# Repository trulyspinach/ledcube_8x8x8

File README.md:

# ledcube_8x8x8

Hobby Compact LED Cube.

Please beware that I'm not a professional electrical enginner, this project is just me having fun. I provide absolutely no warranty for this :)

## The hardware build

My goal is to build a compact LED cube. A lot of cube built i found on Internet is huge(kind of, at least you can't carry them with you), even when the resolution is 8x8x8. So I chose to use small LEDs, and a printed circuit board to hold them together while providing control circuits.

The microcontroller is Atmega32A, the reason of choosing AVR is just because they are simple and really cheap to get, and the 32A model have a fairly enough amount of pins available. Then eight 574s are used for multiplexing IOs. No big deals, pretty simple.

To build this, all you need is around 6 hundreds of LEDs. Only 512 are needed, but when you purchasing cheap LEDs, it is likely that some of them will malfunctions. And some resisitor, caps for the motherboard.

I got all components on local stores and AliExpress, the complete built cost me less than $10(surprisingly cheap huh?).

## Software.

Well, since it is an Atmega32A, you can totaly program it using Arduino IDE(You don't need to).
I haven't had enough time to write some beautiful program yet, but the demo code included is just enough to test and proof your circuit is working.

Yes I will put more code here later..

## Did I made a video ?

Yes, it is here: https://www.bilibili.com/video/av40196289/

The voiceover is me speaking Chinese, but it should be fine.

## Where to get PCBs?

I did included all board layout file in the repo, you can export them with Eagle to some manufactor to made them.
As you know, those manufactors don't really like to just make one board, so I have some spare boards in my hand. I can ship one to you if you live in China, and if by the time you contact me I still have them..

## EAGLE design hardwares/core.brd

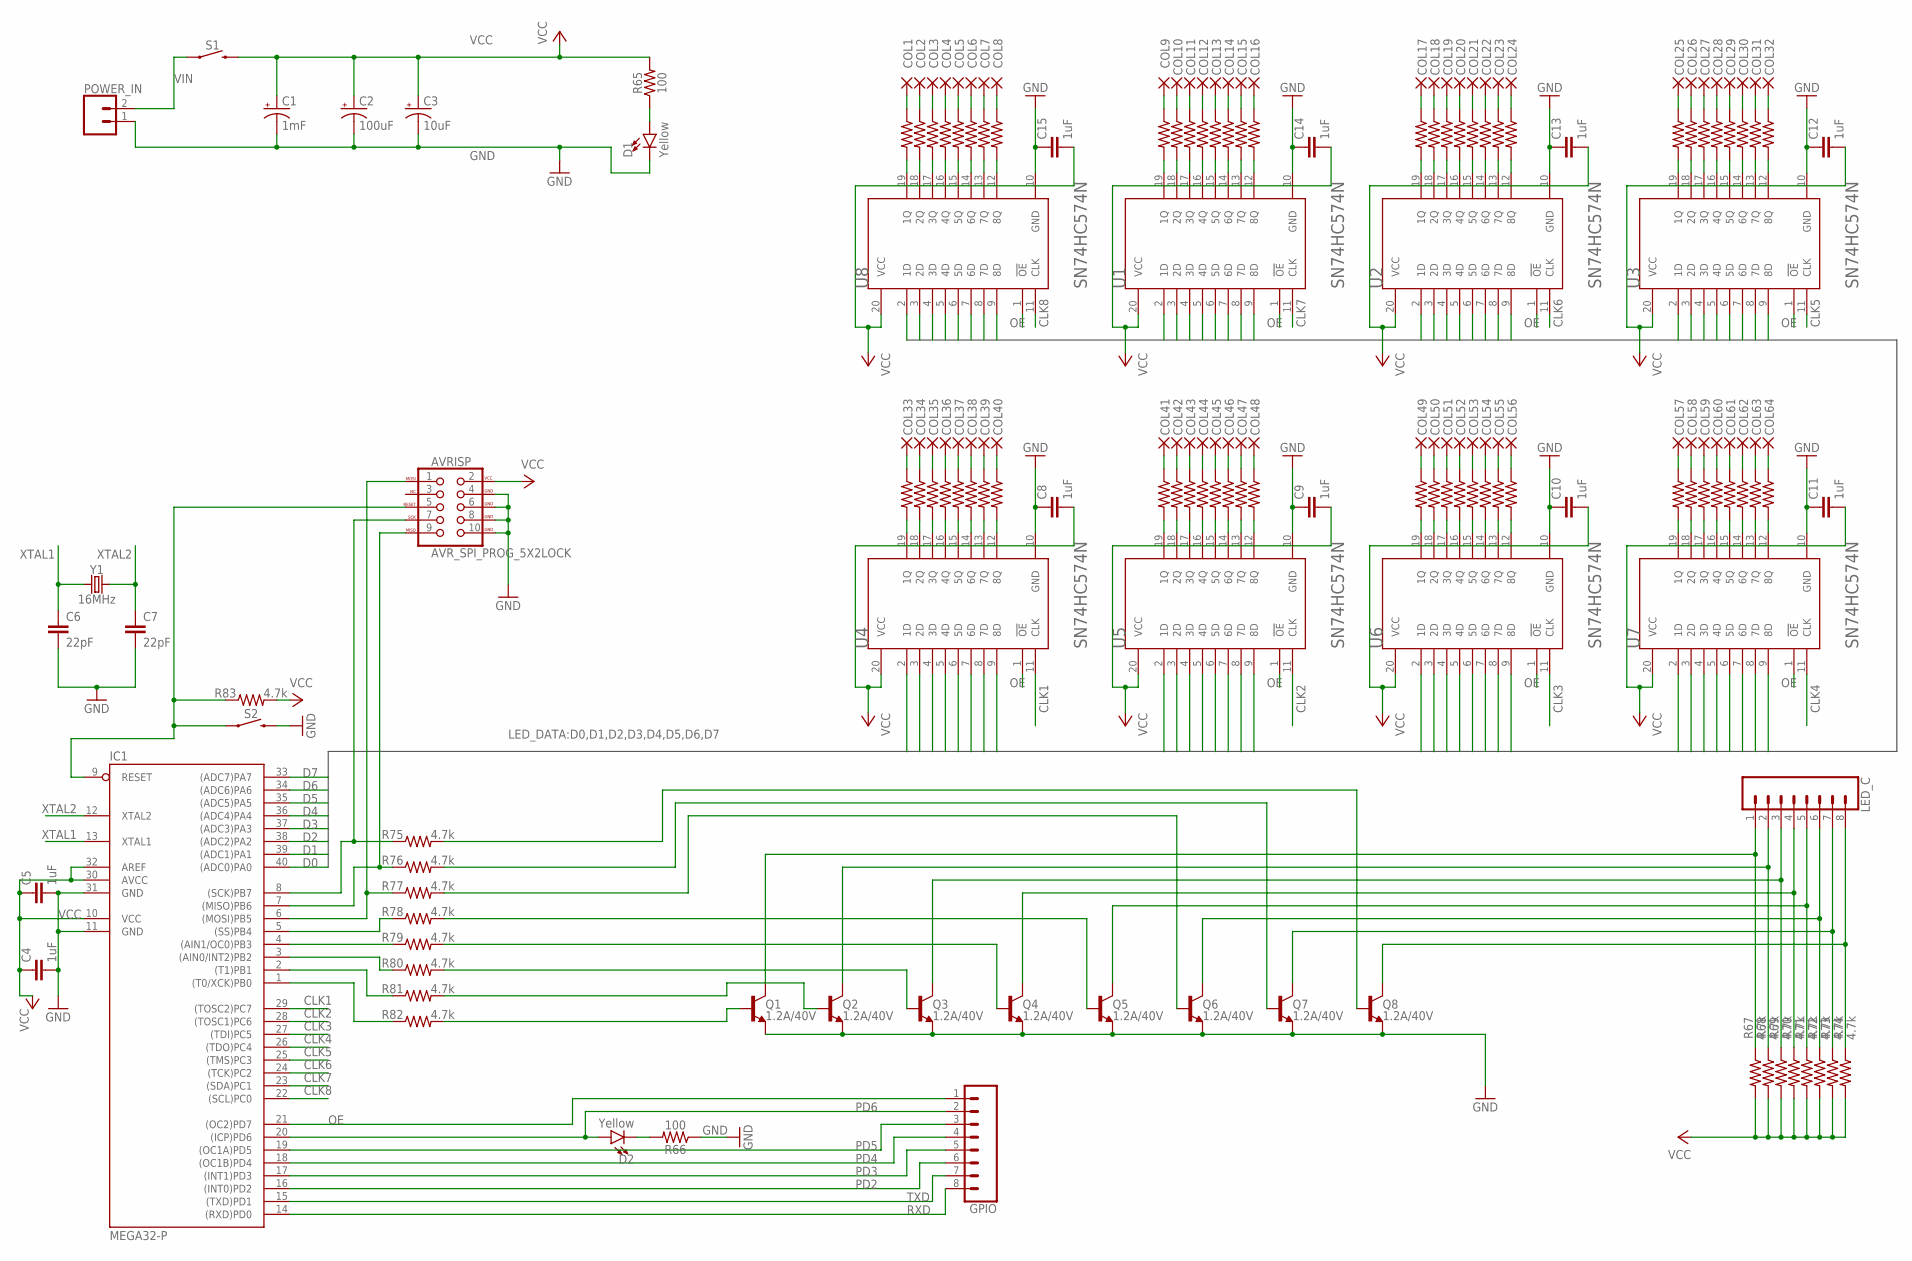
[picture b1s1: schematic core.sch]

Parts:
AVRISP: AVR_SPI_PROG_5X2LOCK; 2X5-SHROUDED_LOCK
C1: 1mF; CPOL-RADIAL-5MM-10MM
C2: 100uF; CPOL-RADIAL-2.5MM-6.5MM
C3: 10uF; CPOL-RADIAL-2.5MM-5MM
C4, C5, C8, C9, C10, C11, C12, C13, C14, C15: 1uF; C2.5-3
C6, C7: 22pF; CAP-PTH-2.54
COL1, COL2, COL3, COL4, COL5, COL6, COL7, COL8, COL9, COL10, COL11, COL12, COL13, COL14, COL15, COL16, COL17, COL18, COL19, COL20, COL21, COL22, COL23, COL24, COL25, COL26, COL27, COL28, COL29, COL30, COL31, COL32, COL33, COL34, COL35, COL36, COL37, COL38, COL39, COL40, COL41, COL42, COL43, COL44, COL45, COL46, COL47, COL48, COL49, COL50, COL51, COL52, COL53, COL54, COL55, COL56, COL57, COL58, COL59, COL60, COL61, COL62, COL63, COL64: 1,6/0,9
D1, D2: Yellow; LED-1206
GPIO: CONN_08"; 1X08
IC1: MEGA32-P; DIL40
LED_C: CONN_08"; 1X08
POWER_IN: CONN_02POLAR; MOLEX-1X2
Q1, Q2, Q3, Q4, Q5, Q6, Q7, Q8: 1.2A/40V; SOT23-3
R1, R2, R3, R4, R5, R6, R7, R8, R9, R10, R11, R12, R13, R14, R15, R16, R17, R18, R19, R20, R21, R22, R23, R24, R25, R26, R27, R28, R29, R30, R31, R32, R33, R34, R35, R36, R37, R38, R39, R40, R41, R42, R43, R44, R45, R46, R47, R48, R49, R50, R51, R52, R53, R54, R55, R56, R57, R58, R59, R60, R61, R62, R63, R64, R65, R66: 100; AXIAL-0.3
R67, R68, R69, R70, R71, R72, R73, R74, R75, R76, R77, R78, R79, R80, R81, R82, R83: 4.7k; AXIAL-0.3
S1: MOMENTARY-SWITCH-SPST-PTH-RIGHT-ANGLE-KIT; TACTILE_SWITCH_PTH_RIGHT_ANGLE_KIT
S2: MOMENTARY-SWITCH-SPST-PTH-6.0MM; TACTILE_SWITCH_PTH_6.0MM
U1, U2, U3, U4, U5, U6, U7, U8: TEXAS_INSTRUMENTS_SN74HC574NTEXAS_INSTRUMENTS_SN7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; TEXAS_INSTRUMENTS_SN74HC574N_0
Y1: 16MHz; HC49US

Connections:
CLK1: IC1.29 ((TOSC2)PC7), U4.11 (CLK)
CLK2: IC1.28 ((TOSC1)PC6), U5.11 (CLK)
CLK3: IC1.27 ((TDI)PC5), U6.11 (CLK)
CLK4: IC1.26 ((TDO)PC4), U7.11 (CLK)
CLK5: IC1.25 ((TMS)PC3), U3.11 (CLK)
CLK6: IC1.24 ((TCK)PC2), U2.11 (CLK)
CLK7: IC1.23 ((SDA)PC1), U1.11 (CLK)
CLK8: IC1.22 ((SCL)PC0), U8.11 (CLK)
D0: IC1.40 ((ADC0)PA0), U1.2 (1D), U2.2 (1D), U3.2 (1D), U4.2 (1D), U5.2 (1D), U6.2 (1D), U7.2 (1D), U8.2 (1D)
D1: IC1.39 ((ADC1)PA1), U1.3 (2D), U2.3 (2D), U3.3 (2D), U4.3 (2D), U5.3 (2D), U6.3 (2D), U7.3 (2D), U8.3 (2D)
D2: IC1.38 ((ADC2)PA2), U1.4 (3D), U2.4 (3D), U3.4 (3D), U4.4 (3D), U5.4 (3D), U6.4 (3D), U7.4 (3D), U8.4 (3D)
D3: IC1.37 ((ADC3)PA3), U1.5 (4D), U2.5 (4D), U3.5 (4D), U4.5 (4D), U5.5 (4D), U6.5 (4D), U7.5 (4D), U8.5 (4D)
D4: IC1.36 ((ADC4)PA4), U1.6 (5D), U2.6 (5D), U3.6 (5D), U4.6 (5D), U5.6 (5D), U6.6 (5D), U7.6 (5D), U8.6 (5D)
D5: IC1.35 ((ADC5)PA5), U1.7 (6D), U2.7 (6D), U3.7 (6D), U4.7 (6D), U5.7 (6D), U6.7 (6D), U7.7 (6D), U8.7 (6D)
D6: IC1.34 ((ADC6)PA6), U1.8 (7D), U2.8 (7D), U3.8 (7D), U4.8 (7D), U5.8 (7D), U6.8 (7D), U7.8 (7D), U8.8 (7D)
D7: IC1.33 ((ADC7)PA7), U1.9 (8D), U2.9 (8D), U3.9 (8D), U4.9 (8D), U5.9 (8D), U6.9 (8D), U7.9 (8D), U8.9 (8D)
GND: AVRISP.4 (GND), AVRISP.6 (GND), AVRISP.8 (GND), AVRISP.10 (GND), C1.-, C2.2 (-), C3.2 (-), C4.2, C5.2, C6.2, C7.2, C8.1, C9.1, C10.1, C11.1, C12.1, C13.1, C14.1, C15.1, D1.C, IC1.11 (GND), IC1.31 (GND), POWER_IN.1, Q1.2 (E), Q2.2 (E), Q3.2 (E), Q4.2 (E), Q5.2 (E), Q6.2 (E), Q7.2 (E), Q8.2 (E), R66.P$1 (1), S2.3 (2), U1.10 (GND), U2.10 (GND), U3.10 (GND), U4.10 (GND), U5.10 (GND), U6.10 (GND), U7.10 (GND), U8.10 (GND)
unnamed: COL1.1, R1.P$1 (1)
unnamed: R1.P$2 (2), U8.19 (1Q)
unnamed: COL2.1, R2.P$1 (1)
unnamed: R2.P$2 (2), U8.18 (2Q)
unnamed: COL3.1, R3.P$1 (1)
unnamed: R3.P$2 (2), U8.17 (3Q)
unnamed: COL4.1, R4.P$1 (1)
unnamed: R4.P$2 (2), U8.16 (4Q)
unnamed: COL5.1, R5.P$1 (1)
unnamed: R5.P$2 (2), U8.15 (5Q)
unnamed: COL6.1, R6.P$1 (1)
unnamed: R6.P$2 (2), U8.14 (6Q)
unnamed: COL7.1, R7.P$1 (1)
unnamed: R7.P$2 (2), U8.13 (7Q)
unnamed: COL8.1, R8.P$1 (1)
unnamed: R8.P$2 (2), U8.12 (8Q)
unnamed: COL9.1, R9.P$1 (1)
unnamed: R9.P$2 (2), U1.19 (1Q)
unnamed: COL10.1, R10.P$1 (1)
unnamed: R10.P$2 (2), U1.18 (2Q)
unnamed: COL11.1, R11.P$1 (1)
unnamed: R11.P$2 (2), U1.17 (3Q)
unnamed: COL12.1, R12.P$1 (1)
unnamed: R12.P$2 (2), U1.16 (4Q)
unnamed: COL13.1, R13.P$1 (1)
unnamed: R13.P$2 (2), U1.15 (5Q)
unnamed: COL14.1, R14.P$1 (1)
unnamed: R14.P$2 (2), U1.14 (6Q)
unnamed: COL15.1, R15.P$1 (1)
unnamed: R15.P$2 (2), U1.13 (7Q)
unnamed: COL16.1, R16.P$1 (1)
unnamed: R16.P$2 (2), U1.12 (8Q)
unnamed: COL17.1, R17.P$1 (1)
unnamed: R17.P$2 (2), U2.19 (1Q)
unnamed: COL18.1, R18.P$1 (1)
unnamed: R18.P$2 (2), U2.18 (2Q)
unnamed: COL19.1, R19.P$1 (1)
unnamed: R19.P$2 (2), U2.17 (3Q)
unnamed: COL20.1, R20.P$1 (1)
unnamed: R20.P$2 (2), U2.16 (4Q)
unnamed: COL21.1, R21.P$1 (1)
unnamed: R21.P$2 (2), U2.15 (5Q)
unnamed: COL22.1, R22.P$1 (1)
unnamed: R22.P$2 (2), U2.14 (6Q)
unnamed: COL23.1, R23.P$1 (1)
unnamed: R23.P$2 (2), U2.13 (7Q)
unnamed: COL24.1, R24.P$1 (1)
unnamed: R24.P$2 (2), U2.12 (8Q)
unnamed: COL25.1, R25.P$1 (1)
unnamed: R25.P$2 (2), U3.19 (1Q)
unnamed: COL26.1, R26.P$1 (1)
unnamed: R26.P$2 (2), U3.18 (2Q)
unnamed: COL27.1, R27.P$1 (1)
unnamed: R27.P$2 (2), U3.17 (3Q)
unnamed: COL28.1, R28.P$1 (1)
unnamed: R28.P$2 (2), U3.16 (4Q)
unnamed: COL29.1, R29.P$1 (1)
unnamed: R29.P$2 (2), U3.15 (5Q)
unnamed: COL30.1, R30.P$1 (1)
unnamed: R30.P$2 (2), U3.14 (6Q)
unnamed: COL31.1, R31.P$1 (1)
unnamed: R31.P$2 (2), U3.13 (7Q)
unnamed: COL32.1, R32.P$1 (1)
unnamed: R32.P$2 (2), U3.12 (8Q)
unnamed: COL33.1, R33.P$1 (1)
unnamed: R33.P$2 (2), U4.19 (1Q)
unnamed: COL34.1, R34.P$1 (1)
unnamed: R34.P$2 (2), U4.18 (2Q)
unnamed: COL35.1, R35.P$1 (1)
unnamed: R35.P$2 (2), U4.17 (3Q)
unnamed: COL36.1, R36.P$1 (1)
unnamed: R36.P$2 (2), U4.16 (4Q)
unnamed: COL37.1, R37.P$1 (1)
unnamed: R37.P$2 (2), U4.15 (5Q)
unnamed: COL38.1, R38.P$1 (1)
unnamed: R38.P$2 (2), U4.14 (6Q)
unnamed: COL39.1, R39.P$1 (1)
unnamed: R39.P$2 (2), U4.13 (7Q)
unnamed: COL40.1, R40.P$1 (1)
unnamed: R40.P$2 (2), U4.12 (8Q)
unnamed: COL41.1, R41.P$1 (1)
unnamed: R41.P$2 (2), U5.19 (1Q)
unnamed: COL42.1, R42.P$1 (1)
unnamed: R42.P$2 (2), U5.18 (2Q)
unnamed: COL43.1, R43.P$1 (1)
unnamed: R43.P$2 (2), U5.17 (3Q)
unnamed: COL44.1, R44.P$1 (1)
unnamed: R44.P$2 (2), U5.16 (4Q)
unnamed: COL45.1, R45.P$1 (1)
unnamed: R45.P$2 (2), U5.15 (5Q)
unnamed: COL46.1, R46.P$1 (1)
unnamed: R46.P$2 (2), U5.14 (6Q)
unnamed: COL47.1, R47.P$1 (1)
unnamed: R47.P$2 (2), U5.13 (7Q)
unnamed: COL48.1, R48.P$1 (1)
unnamed: R48.P$2 (2), U5.12 (8Q)
unnamed: COL49.1, R49.P$1 (1)
unnamed: R49.P$2 (2), U6.19 (1Q)
unnamed: COL50.1, R50.P$1 (1)
unnamed: R50.P$2 (2), U6.18 (2Q)
unnamed: COL51.1, R51.P$1 (1)
unnamed: R51.P$2 (2), U6.17 (3Q)
unnamed: COL52.1, R52.P$1 (1)
unnamed: R52.P$2 (2), U6.16 (4Q)
unnamed: COL53.1, R53.P$1 (1)
unnamed: R53.P$2 (2), U6.15 (5Q)
unnamed: COL54.1, R54.P$1 (1)
unnamed: R54.P$2 (2), U6.14 (6Q)
unnamed: COL55.1, R55.P$1 (1)
unnamed: R55.P$2 (2), U6.13 (7Q)
unnamed: COL56.1, R56.P$1 (1)
unnamed: R56.P$2 (2), U6.12 (8Q)
unnamed: COL57.1, R57.P$1 (1)
unnamed: R57.P$2 (2), U7.19 (1Q)
unnamed: COL58.1, R58.P$1 (1)
unnamed: R58.P$2 (2), U7.18 (2Q)
unnamed: COL59.1, R59.P$1 (1)
unnamed: R59.P$2 (2), U7.17 (3Q)
unnamed: COL60.1, R60.P$1 (1)
unnamed: R60.P$2 (2), U7.16 (4Q)
unnamed: COL61.1, R61.P$1 (1)
unnamed: R61.P$2 (2), U7.15 (5Q)
unnamed: COL62.1, R62.P$1 (1)
unnamed: R62.P$2 (2), U7.14 (6Q)
unnamed: COL63.1, R63.P$1 (1)
unnamed: R63.P$2 (2), U7.13 (7Q)
unnamed: COL64.1, R64.P$1 (1)
unnamed: R64.P$2 (2), U7.12 (8Q)
unnamed: D1.A, R65.P$1 (1)
unnamed: D2.C, R66.P$2 (2)
unnamed: LED_C.1, Q1.3 (C), R67.P$1 (1)
unnamed: LED_C.2, Q2.3 (C), R68.P$1 (1)
unnamed: LED_C.3, Q3.3 (C), R69.P$1 (1)
unnamed: LED_C.4, Q4.3 (C), R70.P$1 (1)
unnamed: LED_C.5, Q5.3 (C), R71.P$1 (1)
unnamed: LED_C.6, Q6.3 (C), R72.P$1 (1)
unnamed: LED_C.7, Q7.3 (C), R73.P$1 (1)
unnamed: LED_C.8, Q8.3 (C), R74.P$1 (1)
unnamed: IC1.1 ((T0/XCK)PB0), R82.P$1 (1)
unnamed: IC1.2 ((T1)PB1), R81.P$1 (1)
unnamed: IC1.3 ((AIN0/INT2)PB2), R80.P$1 (1)
unnamed: IC1.4 ((AIN1/OC0)PB3), R79.P$1 (1)
unnamed: IC1.5 ((SS)PB4), R78.P$1 (1)
unnamed: AVRISP.1 (MOSI), IC1.6 ((MOSI)PB5), R77.P$1 (1)
unnamed: AVRISP.9 (MISO), IC1.7 ((MISO)PB6), R76.P$1 (1)
unnamed: AVRISP.7 (SCK), IC1.8 ((SCK)PB7), R75.P$1 (1)
unnamed: Q1.1 (B), R82.P$2 (2)
unnamed: Q2.1 (B), R81.P$2 (2)
unnamed: Q6.1 (B), R77.P$2 (2)
unnamed: Q3.1 (B), R80.P$2 (2)
unnamed: Q4.1 (B), R79.P$2 (2)
unnamed: Q5.1 (B), R78.P$2 (2)
unnamed: Q7.1 (B), R76.P$2 (2)
unnamed: Q8.1 (B), R75.P$2 (2)
unnamed: AVRISP.5 (RESET), IC1.9 (RESET), R83.P$1 (1), S2.1
OE: GPIO.1, IC1.21 ((OC2)PD7), U1.1 (!OE!), U2.1 (!OE!), U3.1 (!OE!), U4.1 (!OE!), U5.1 (!OE!), U6.1 (!OE!), U7.1 (!OE!), U8.1 (!OE!)
PD2: GPIO.6, IC1.16 ((INT0)PD2)
PD3: GPIO.5, IC1.17 ((INT1)PD3)
PD4: GPIO.4, IC1.18 ((OC1B)PD4)
PD5: GPIO.3, IC1.19 ((OC1A)PD5)
PD6: D2.A, GPIO.2, IC1.20 ((ICP)PD6)
RXD: GPIO.8, IC1.14 ((RXD)PD0)
TXD: GPIO.7, IC1.15 ((TXD)PD1)
VCC: AVRISP.2 (VCC), C1.+, C2.1 (+), C3.1 (+), C4.1, C5.1, C8.2, C9.2, C10.2, C11.2, C12.2, C13.2, C14.2, C15.2, IC1.10 (VCC), IC1.30 (AVCC), IC1.32 (AREF), R65.P$2 (2), R67.P$2 (2), R68.P$2 (2), R69.P$2 (2), R70.P$2 (2), R71.P$2 (2), R72.P$2 (2), R73.P$2 (2), R74.P$2 (2), R83.P$2 (2), S1.2, U1.20 (VCC), U2.20 (VCC), U3.20 (VCC), U4.20 (VCC), U5.20 (VCC), U6.20 (VCC), U7.20 (VCC), U8.20 (VCC)
VIN: POWER_IN.2, S1.1
XTAL1: C6.1, IC1.13 (XTAL1), Y1.1
XTAL2: C7.1, IC1.12 (XTAL2), Y1.2

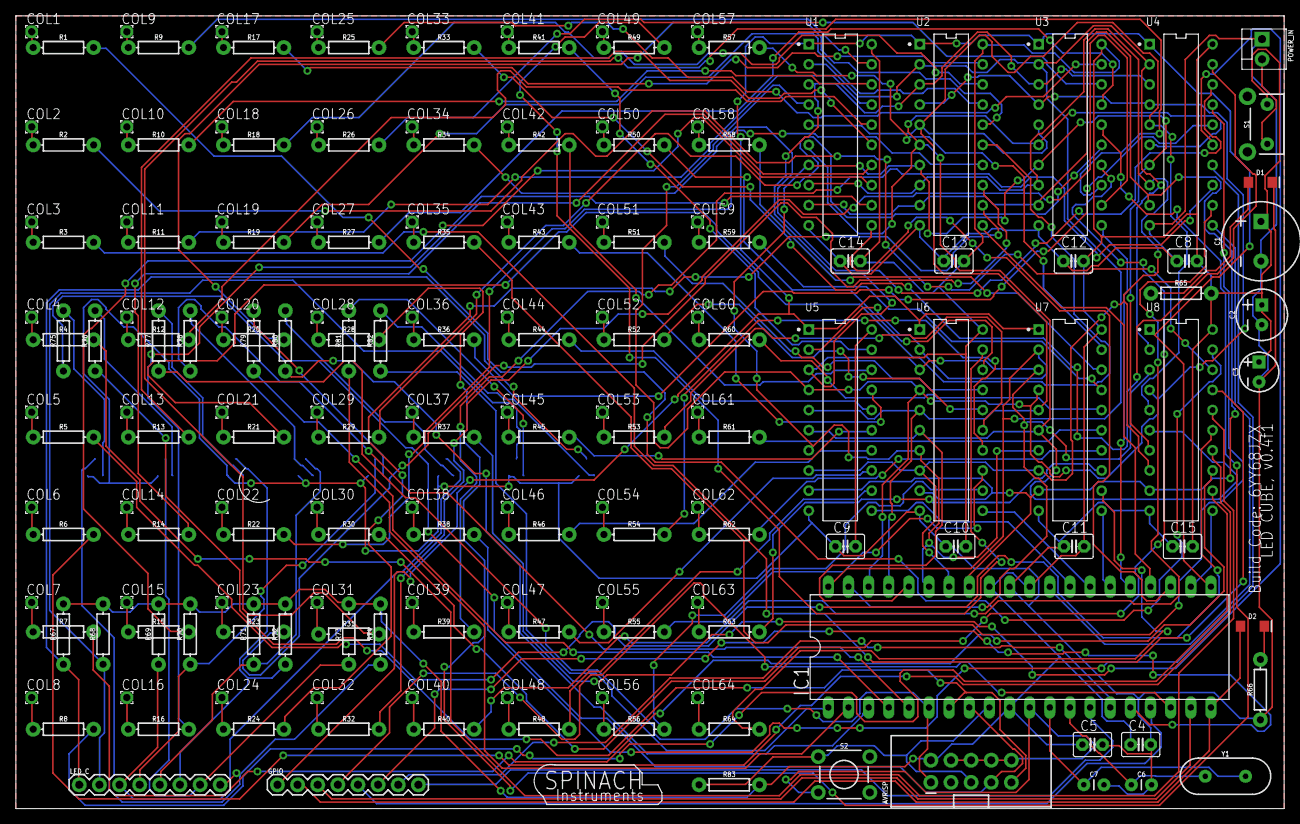
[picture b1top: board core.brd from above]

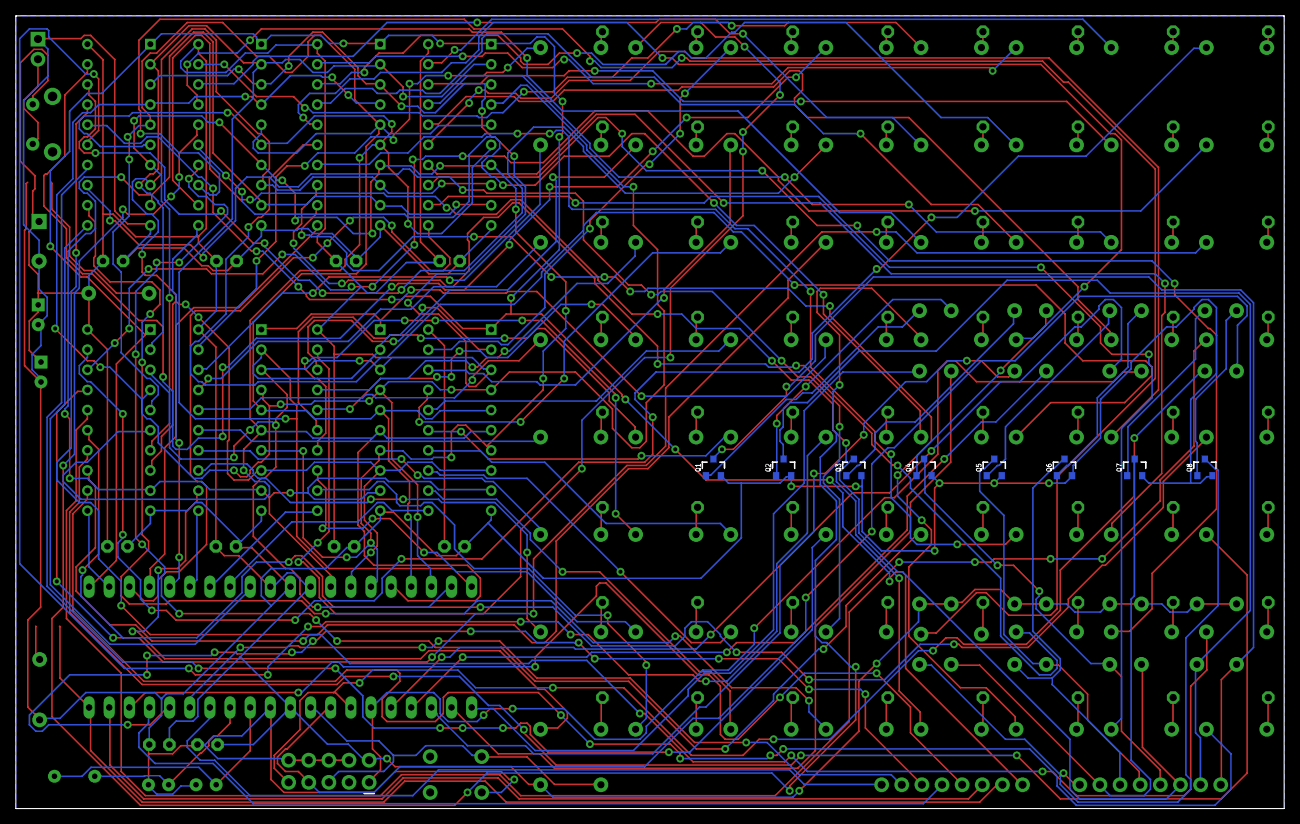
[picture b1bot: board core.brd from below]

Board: 2 copper layers, 160.0 x 100.0 mm, 188 parts (8 on the bottom side), 184 nets.

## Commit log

2019-01-09 push init files
2019-01-09 fix number, lol
2019-01-22 add game of life v0.1

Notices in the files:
parts and their libraries:
SparkFun-Connectors: Licensing: Creative Commons ShareAlike 4.0 International - https://creativecommons.org/licenses/by-sa/4.0
